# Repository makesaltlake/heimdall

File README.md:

# Heimdall

Heimdall is [Make Salt Lake](https://makesaltlake.org)'s member management and access control system. It consists of a few different parts:

  - [Firmware](firmware) intended to run on an [ESP32](https://en.wikipedia.org/wiki/ESP32), one per door or other device that needs access control.
  - [PCB designs](hardware) that can be used to make the physical badge readers.

### 
Join [Make Salt Lake's Slack team](https://slack.makesaltlake.org/), then head over to [#rfid-strikeforce](https://app.slack.com/client/T16JZCGBY/CGDLBCCCT) if you'd like to get in touch.

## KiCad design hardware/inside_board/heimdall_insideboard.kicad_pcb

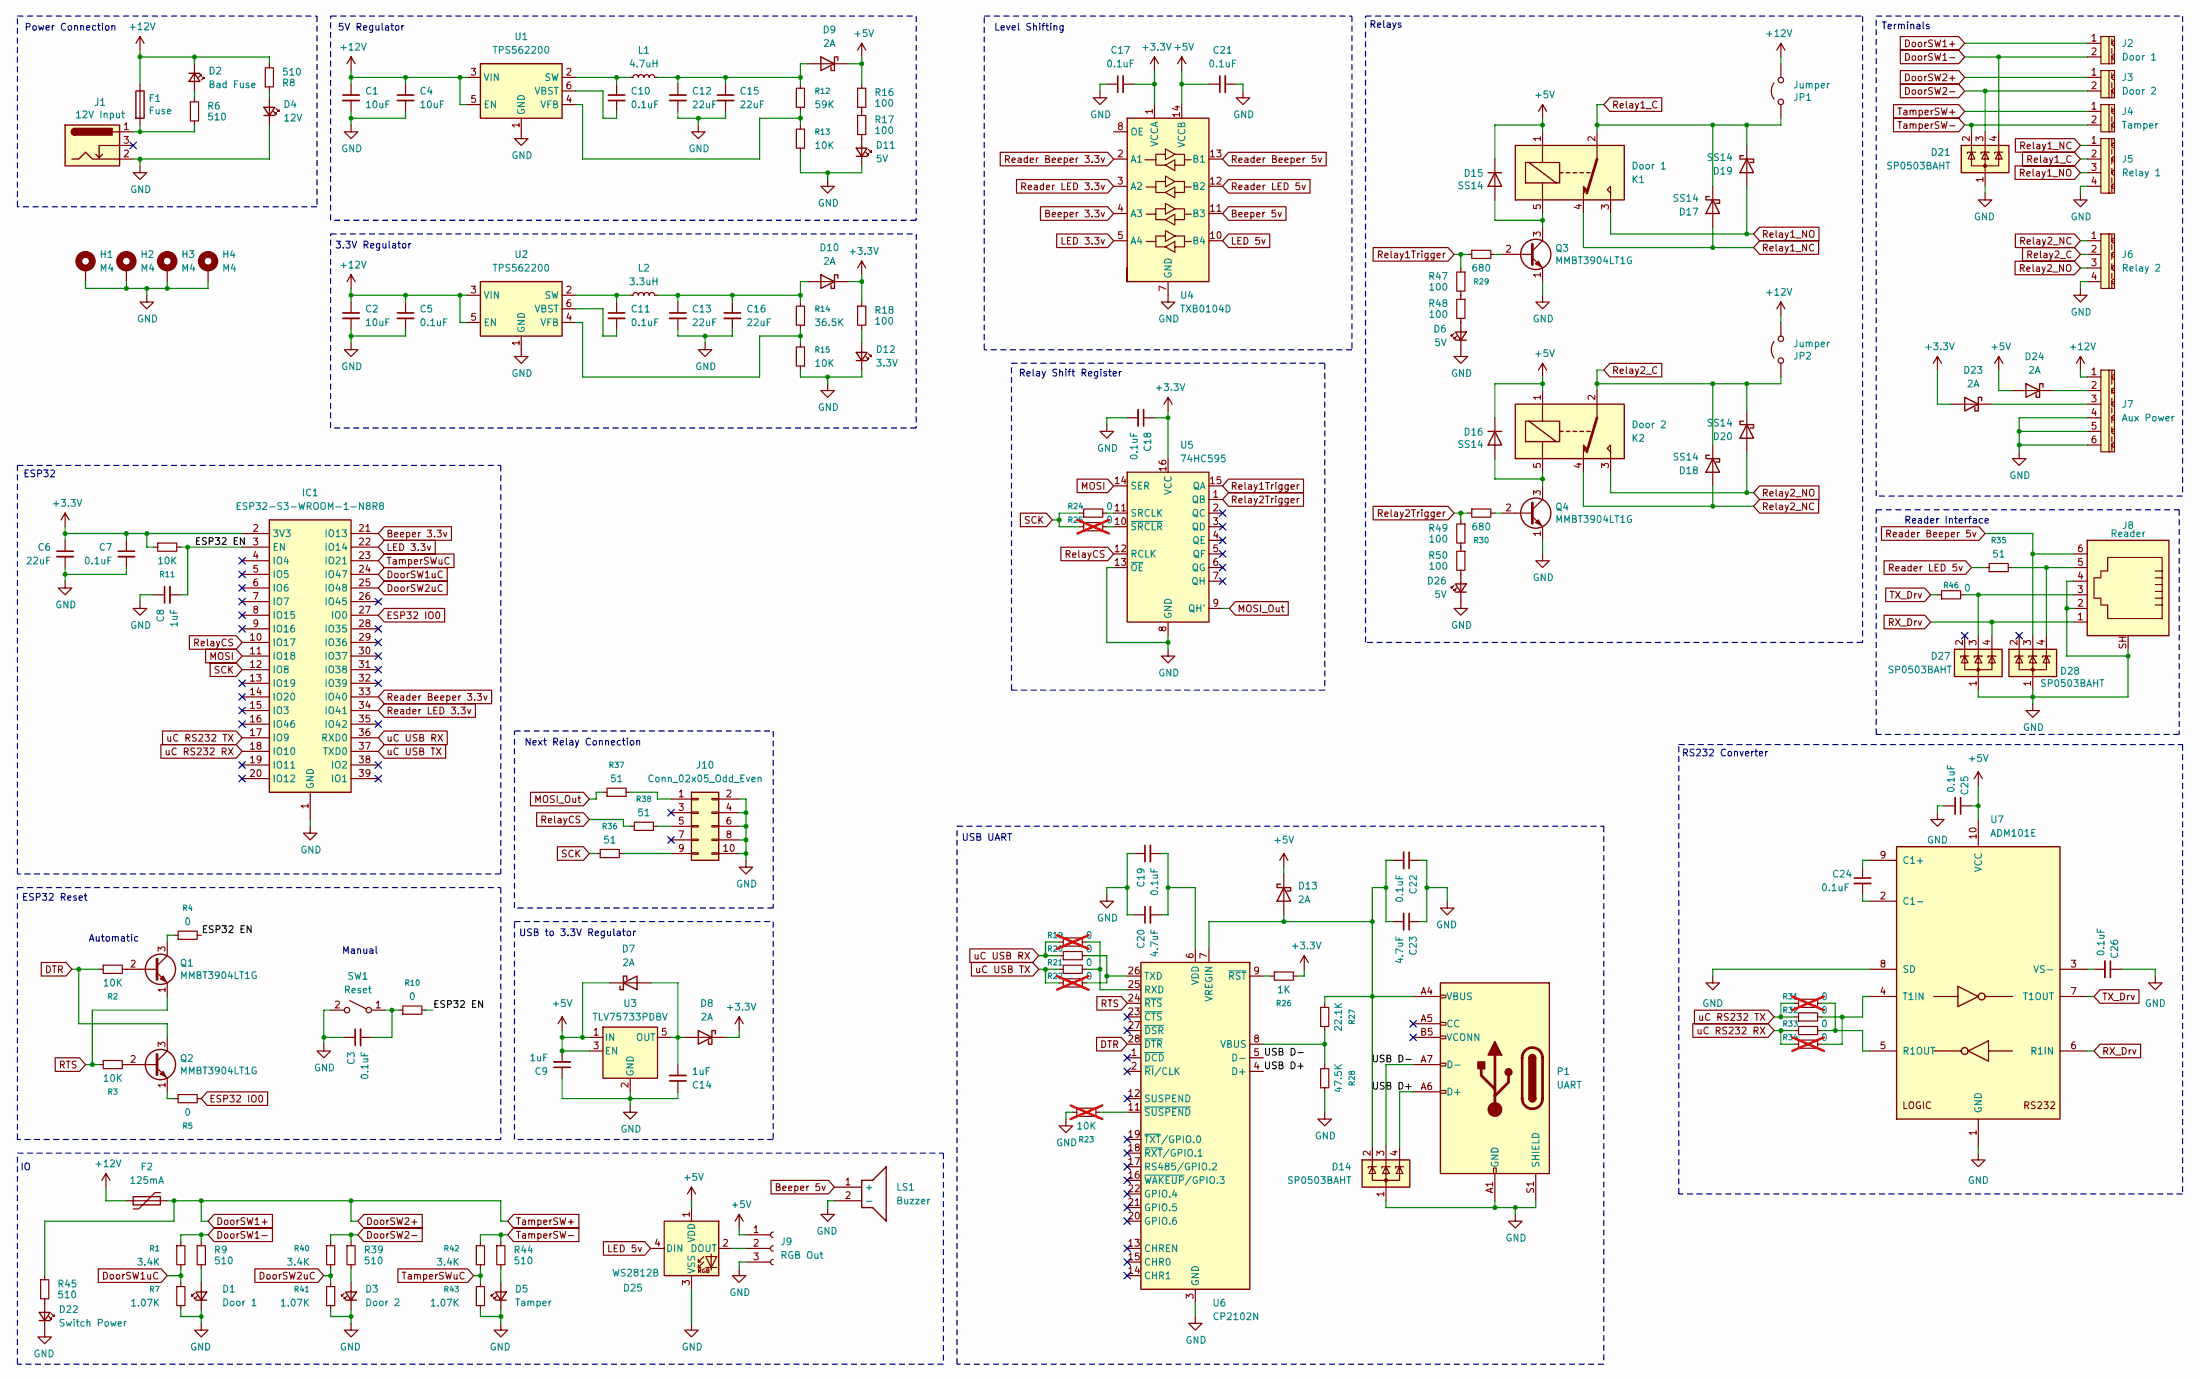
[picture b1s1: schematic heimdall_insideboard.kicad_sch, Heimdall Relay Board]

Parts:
C1, C2, C4: 10uF; C_0805_2012Metric
C3, C5, C7, C10, C11, C17, C18, C19, C21, C22, C24, C25, C26: 0.1uF; C_0805_2012Metric
C6, C12, C13, C15, C16: 22uF; C_0805_2012Metric
C8, C9, C14: 1uF; C_0805_2012Metric
C20, C23: 4.7uF; C_0805_2012Metric
D1: Door 1; LED_0805_2012Metric
D2: Bad Fuse; LED_0805_2012Metric
D3: Door 2; LED_0805_2012Metric
D4: 12V; LED_0805_2012Metric
D5: Tamper; LED_0805_2012Metric
D6, D11, D26: 5V; LED_0805_2012Metric
D7, D8, D9, D10, D13, D23, D24: 2A; D_SMB
D12: 3.3V; LED_0805_2012Metric
D14, D21, D27, D28: SP0503BAHT; SOT-143
D15, D16, D17, D18, D19, D20: SS14; D_SMA
D22: Switch Power; LED_0805_2012Metric
D25: WS2812B; LED_WS2812B_PLCC4_5.0x5.0mm_P3.2mm
F1: Fuse; Fuseholder_Clip-5x20mm_Littelfuse_521_Lateral_P17.00x5.00mm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
F2: 125mA; Fuse_1206_3216Metric
H1, H2, H3, H4: M4; MountingHole_4.3mm_M4_Pad_Via
IC1: ESP32-S3-WROOM-1-N8R8; ESP32S3WROOM1N8R8; Mouser Part Number 356-EP32S3WROOM1N8R8
J1: 12V Input; BarrelJack_Wuerth_6941xx301002
J2: Door 1; 1759017
J3: Door 2; 1759017
J4: Tamper; 1759017
J5: Relay 1; 1759033
J6: Relay 2; 1759033
J7: Aux Power; 1759059
J8: Reader; CRJ0241TH
J9: RGB Out; PinHeader_1x03_P2.54mm_Vertical
J10: Conn_02x05_Odd_Even; 75869-101LF
JP1, JP2: Jumper; PinHeader_1x03_P2.54mm_Vertical
K1: Door 1; G6RN17EASICFHADC5; Manufacturer_Part_Number G6RN-17-E-ASI-CF-HA DC5
K2: Door 2; G6RN17EASICFHADC5; Manufacturer_Part_Number G6RN-17-E-ASI-CF-HA DC5
L1: 4.7uH; SRR1260A4R7Y
L2: 3.3uH; SRR1260A4R7Y
LS1: Buzzer; CMT1075SMTTR; Mouser Part Number 490-CMT-1075-SMT-TR
P1: UART; USB4920-00-A
Q1, Q2, Q3, Q4: MMBT3904LT1G; SOT-23-3
R1, R40, R42: 3.4K; R_0805_2012Metric
R2, R3, R11, R13, R15: 10K; R_0805_2012Metric
R4, R5, R10, R20, R21, R24, R32, R33, R46: 0; R_0805_2012Metric
R6, R8, R9, R39, R44, R45: 510; R_0805_2012Metric
R7, R41, R43: 1.07K; R_0805_2012Metric
R12: 59K; R_0805_2012Metric
R14: 36.5K; R_0805_2012Metric
R16, R17, R18, R47, R48, R49, R50: 100; R_0805_2012Metric
R19, R22, R25, R31, R34: 0; R_0805_2012Metric; not fitted
R23: 10K; R_0805_2012Metric; not fitted
R26: 1K; R_0805_2012Metric
R27: 22.1K; R_0805_2012Metric
R28: 47.5K; R_0805_2012Metric
R29, R30: 680; R_0805_2012Metric
R35, R36, R37, R38: 51; R_0805_2012Metric
SW1: Reset; SW_SPST_Omron_B3FS-100xP
U1, U2: TPS562200; SOT-23-6
U3: TLV75733PDBV; SOT-23-5
U4: TXB0104D; SOIC-14_3.9x8.7mm_P1.27mm
U5: 74HC595; SOIC-16W_7.5x10.3mm_P1.27mm
U6: CP2102N; QFN-28-1EP_5x5mm_P0.5mm_EP3.35x3.35mm
U7: ADM101E; MSOP-10_3x3mm_P0.5mm

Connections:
+3.3V: C6.1, C7.1, C17.2, C18.1, D8.1 (K), D10.1 (K), D23.2 (A), IC1.2 (3V3), R11.1, R18.1, R26.2, U4.1 (VCCA), U5.16 (VCC)
+5V: C9.2, C21.1, C25.1, D7.1 (K), D9.1 (K), D13.1 (K), D15.1 (K), D16.1 (K), D24.2 (A), D25.1 (VDD), J9.1, K1.1, K2.1, R16.1, U3.1 (IN), U3.3 (EN), U4.14 (VCCB), U7.10 (VCC)
+12V: C1.1, C2.1, C4.1, C5.1, D2.1 (K), F1.1, F2.1, J7.1, JP1.1 (A), JP2.1 (A), R8.2, U1.3 (VIN), U1.5 (EN), U2.3 (VIN), U2.5 (EN)
/ESP32 EN: C8.2, IC1.3 (EN), R4.2, R10.2, R11.2
/USB D+: D14.4 (K), P1.A6 (D+), U6.4 (D+)
/USB D-: D14.3 (K), P1.A7 (D-), U6.5 (D-)
Beeper 3.3v: IC1.21 (IO13), U4.4 (A3)
Beeper 5v: LS1.1 (+), U4.11 (B3)
DTR: Q2.3 (C), R2.1, U6.28 (~DTR)
DoorSW1+: F2.2, J2.1, J3.1, J4.1, R45.1
DoorSW1-: D21.4 (K), J2.2, R1.1, R9.1
DoorSW1uC: IC1.24 (IO47), R1.2, R7.1
DoorSW2-: D21.3 (K), J3.2, R39.1, R40.1
DoorSW2uC: IC1.25 (IO48), R40.2, R41.1
ESP32 IO0: IC1.27 (IO0), R5.2
GND: C1.2, C2.2, C3.1, C4.2, C5.2, C6.2, C7.2, C8.1, C9.1, C12.2, C13.2, C14.1, C15.2, C16.2, C17.1, C18.2, C19.1, C20.1, C21.2, C22.1, C23.1, C25.2, C26.1, D1.1 (K), D3.1 (K), D4.1 (K), D5.1 (K), D6.1 (K), D11.1 (K), D12.1 (K), D14.1 (A), D21.1 (A), D22.1 (K), D25.3 (VSS), D26.1 (K), D27.1 (A), D28.1 (A), H1.1, H2.1, H3.1, H4.1, IC1.1 (GND), J1.2, J5.4, J6.4, J7.4, J7.5, J7.6, J8.2, J8.4, J8.SH, J9.3, J10.2, J10.4, J10.6, J10.8, J10.10, LS1.2 (-), P1.A1 (GND), P1.A12 (GND), P1.B1 (GND), P1.B12 (GND), P1.S1 (SHIELD), Q3.1 (E), Q4.1 (E), R7.2, R13.1, R15.1, R23.1, R28.1, R41.2, R43.2, SW1.2 (B), U1.1 (GND), U2.1 (GND), U3.2 (GND), U4.7 (GND), U5.8 (GND), U5.13 (~OE), U6.3 (GND), U6.29 (GND), U7.1 (GND), U7.8 (SD)
LED 3.3v: IC1.22 (IO14), U4.5 (A4)
LED 5v: D25.4 (DIN), U4.10 (B4)
MOSI: IC1.11 (IO18), U5.14 (SER)
MOSI_Out: R37.1, U5.9 (QH')
unnamed: D1.2 (A), R9.2
unnamed: D2.2 (A), R6.1
unnamed: D3.2 (A), R39.2
unnamed: D4.2 (A), R8.1
unnamed: D5.2 (A), R44.2
unnamed: D6.2 (A), R48.2
unnamed: C14.2, D7.2 (A), D8.2 (A), U3.5 (OUT)
unnamed: C12.1, C15.1, D9.2 (A), L1.2, R12.2
unnamed: C13.1, C16.1, D10.2 (A), L2.2, R14.2
unnamed: D11.2 (A), R17.2
unnamed: D12.2 (A), R18.2
unnamed: C22.2, C23.2, D13.2 (A), D14.2 (K), P1.A4 (VBUS), P1.A9 (VBUS), P1.B4 (VBUS), P1.B9 (VBUS), R27.2, U6.7 (VREGIN)
unnamed: D15.2 (A), K1.5, Q3.3 (C)
unnamed: D16.2 (A), K2.5, Q4.3 (C)
unnamed: D22.2 (A), R45.2
unnamed: D23.1 (K), J7.3
unnamed: D24.1 (K), J7.2
unnamed: D25.2 (DOUT), J9.2
unnamed: D26.2 (A), R50.2
unnamed: D27.3 (K), J8.3, R46.2
unnamed: D28.4 (K), J8.5, R35.2
unnamed: F1.2, J1.1, R6.2
unnamed: J10.1, R37.2
unnamed: J10.5, R38.2
unnamed: J10.9, R36.2
unnamed: Q1.2 (B), R2.2
unnamed: Q1.3 (C), R4.1
unnamed: Q2.2 (B), R3.2
unnamed: Q2.1 (E), R5.1
unnamed: Q3.2 (B), R29.2
unnamed: Q4.2 (B), R30.2
unnamed: R16.2, R17.1
unnamed: R47.2, R48.1
unnamed: R49.2, R50.1
unnamed: C3.2, R10.1, SW1.1 (A)
unnamed: C10.1, L1.1, U1.2 (SW)
unnamed: C10.2, U1.6 (VBST)
unnamed: R12.1, R13.2, U1.4 (VFB)
unnamed: C11.1, L2.1, U2.2 (SW)
unnamed: C11.2, U2.6 (VBST)
unnamed: R14.1, R15.2, U2.4 (VFB)
unnamed: R24.2, U5.11 (SRCLK)
unnamed: R25.2, U5.10 (~SRCLR)
unnamed: R19.2, R21.2, U6.25 (RXD)
unnamed: R20.2, R22.2, U6.26 (TXD)
unnamed: R27.1, R28.2, U6.8 (VBUS)
unnamed: C19.2, C20.2, U6.6 (VDD)
unnamed: R26.1, U6.9 (~RST)
unnamed: R23.2, U6.11 (~SUSPEND)
unnamed: C24.1, U7.9 (C1+)
unnamed: C24.2, U7.2 (C1-)
unnamed: R31.2, R33.2, U7.5 (R1OUT)
unnamed: R32.2, R34.2, U7.4 (T1IN)
unnamed: C26.2, U7.3 (VS-)
RTS: Q1.1 (E), R3.1, U6.24 (~RTS)
RX_Drv: D27.4 (K), J8.1, U7.6 (R1IN)
Reader Beeper 3.3v: IC1.33 (IO40), U4.2 (A1)
Reader Beeper 5v: D28.3 (K), J8.6, U4.13 (B1)
Reader LED 3.3v: IC1.34 (IO41), U4.3 (A2)
Reader LED 5v: R35.1, U4.12 (B2)
Relay1Trigger: R29.1, R47.1, U5.15 (QA)
Relay1_C: D17.1 (K), D19.1 (K), J5.2, JP1.2 (B), K1.2
Relay1_NC: D17.2 (A), J5.1, K1.4
Relay1_NO: D19.2 (A), J5.3, K1.3
Relay2Trigger: R30.1, R49.1, U5.1 (QB)
Relay2_C: D18.1 (K), D20.1 (K), J6.2, JP2.2 (B), K2.2
Relay2_NC: D18.2 (A), J6.1, K2.4
Relay2_NO: D20.2 (A), J6.3, K2.3
RelayCS: IC1.10 (IO17), R38.1, U5.12 (RCLK)
SCK: IC1.12 (IO8), R24.1, R25.1, R36.1
TX_Drv: R46.1, U7.7 (T1OUT)
TamperSW-: D21.2 (K), J4.2, R42.1, R44.1
TamperSWuC: IC1.23 (IO21), R42.2, R43.1
uC RS232 RX: IC1.18 (IO10), R33.1, R34.1
uC RS232 TX: IC1.17 (IO9), R31.1, R32.1
uC USB RX: IC1.36 (RXD0), R19.1, R20.1
uC USB TX: IC1.37 (TXD0), R21.1, R22.1

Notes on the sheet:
Power Connection
Relay Shift Register
Automatic
RS232 Converter
ESP32 Reset
USB to 3.3V Regulator
Terminals
Next Relay Connection
Manual
3.3V Regulator
5V Regulator
Reader Interface
Relays
Level Shifting
USB UART
ESP32

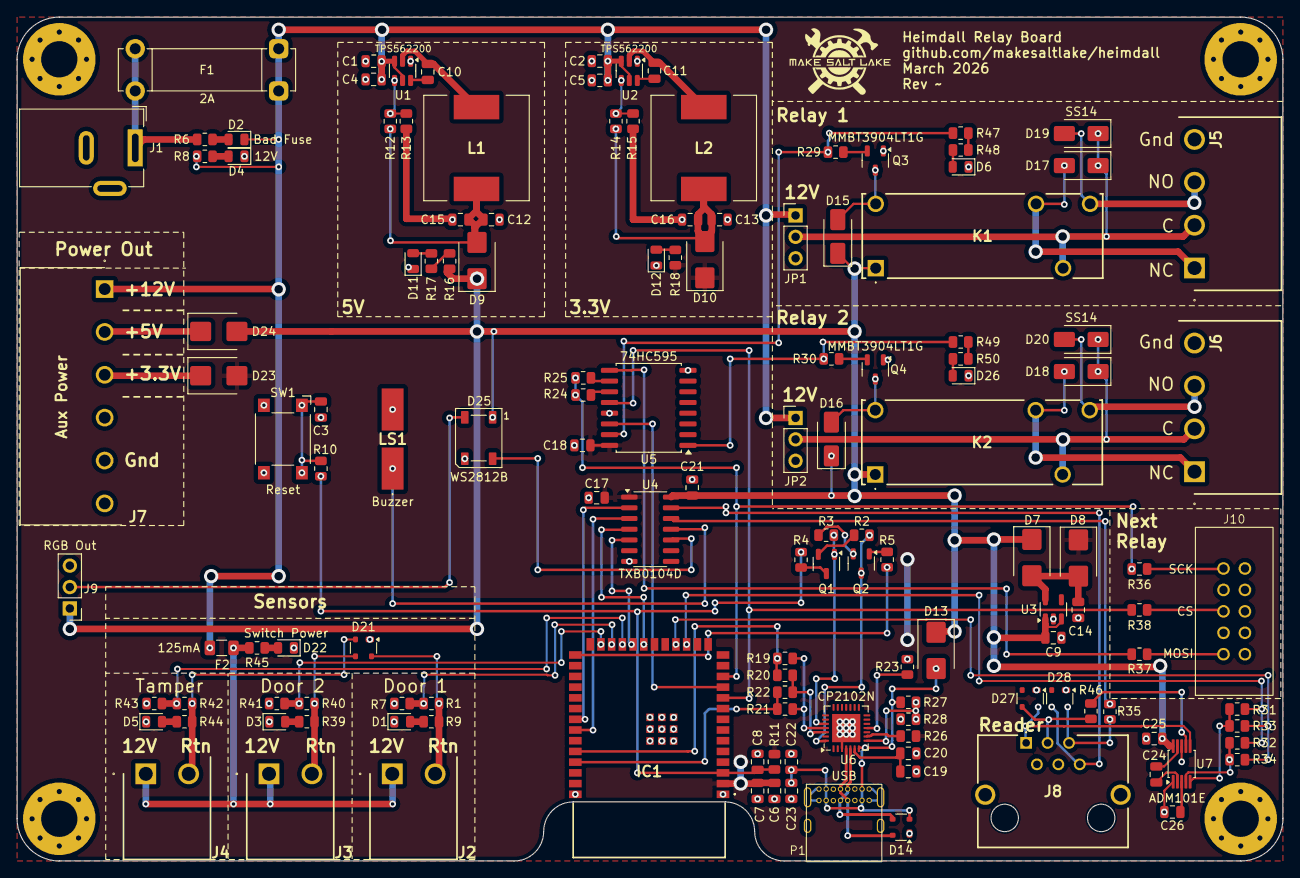
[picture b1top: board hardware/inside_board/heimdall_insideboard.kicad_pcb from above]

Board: 2 copper layers, 150.0 x 100.0 mm, 141 parts (0 on the bottom side), 97 nets.

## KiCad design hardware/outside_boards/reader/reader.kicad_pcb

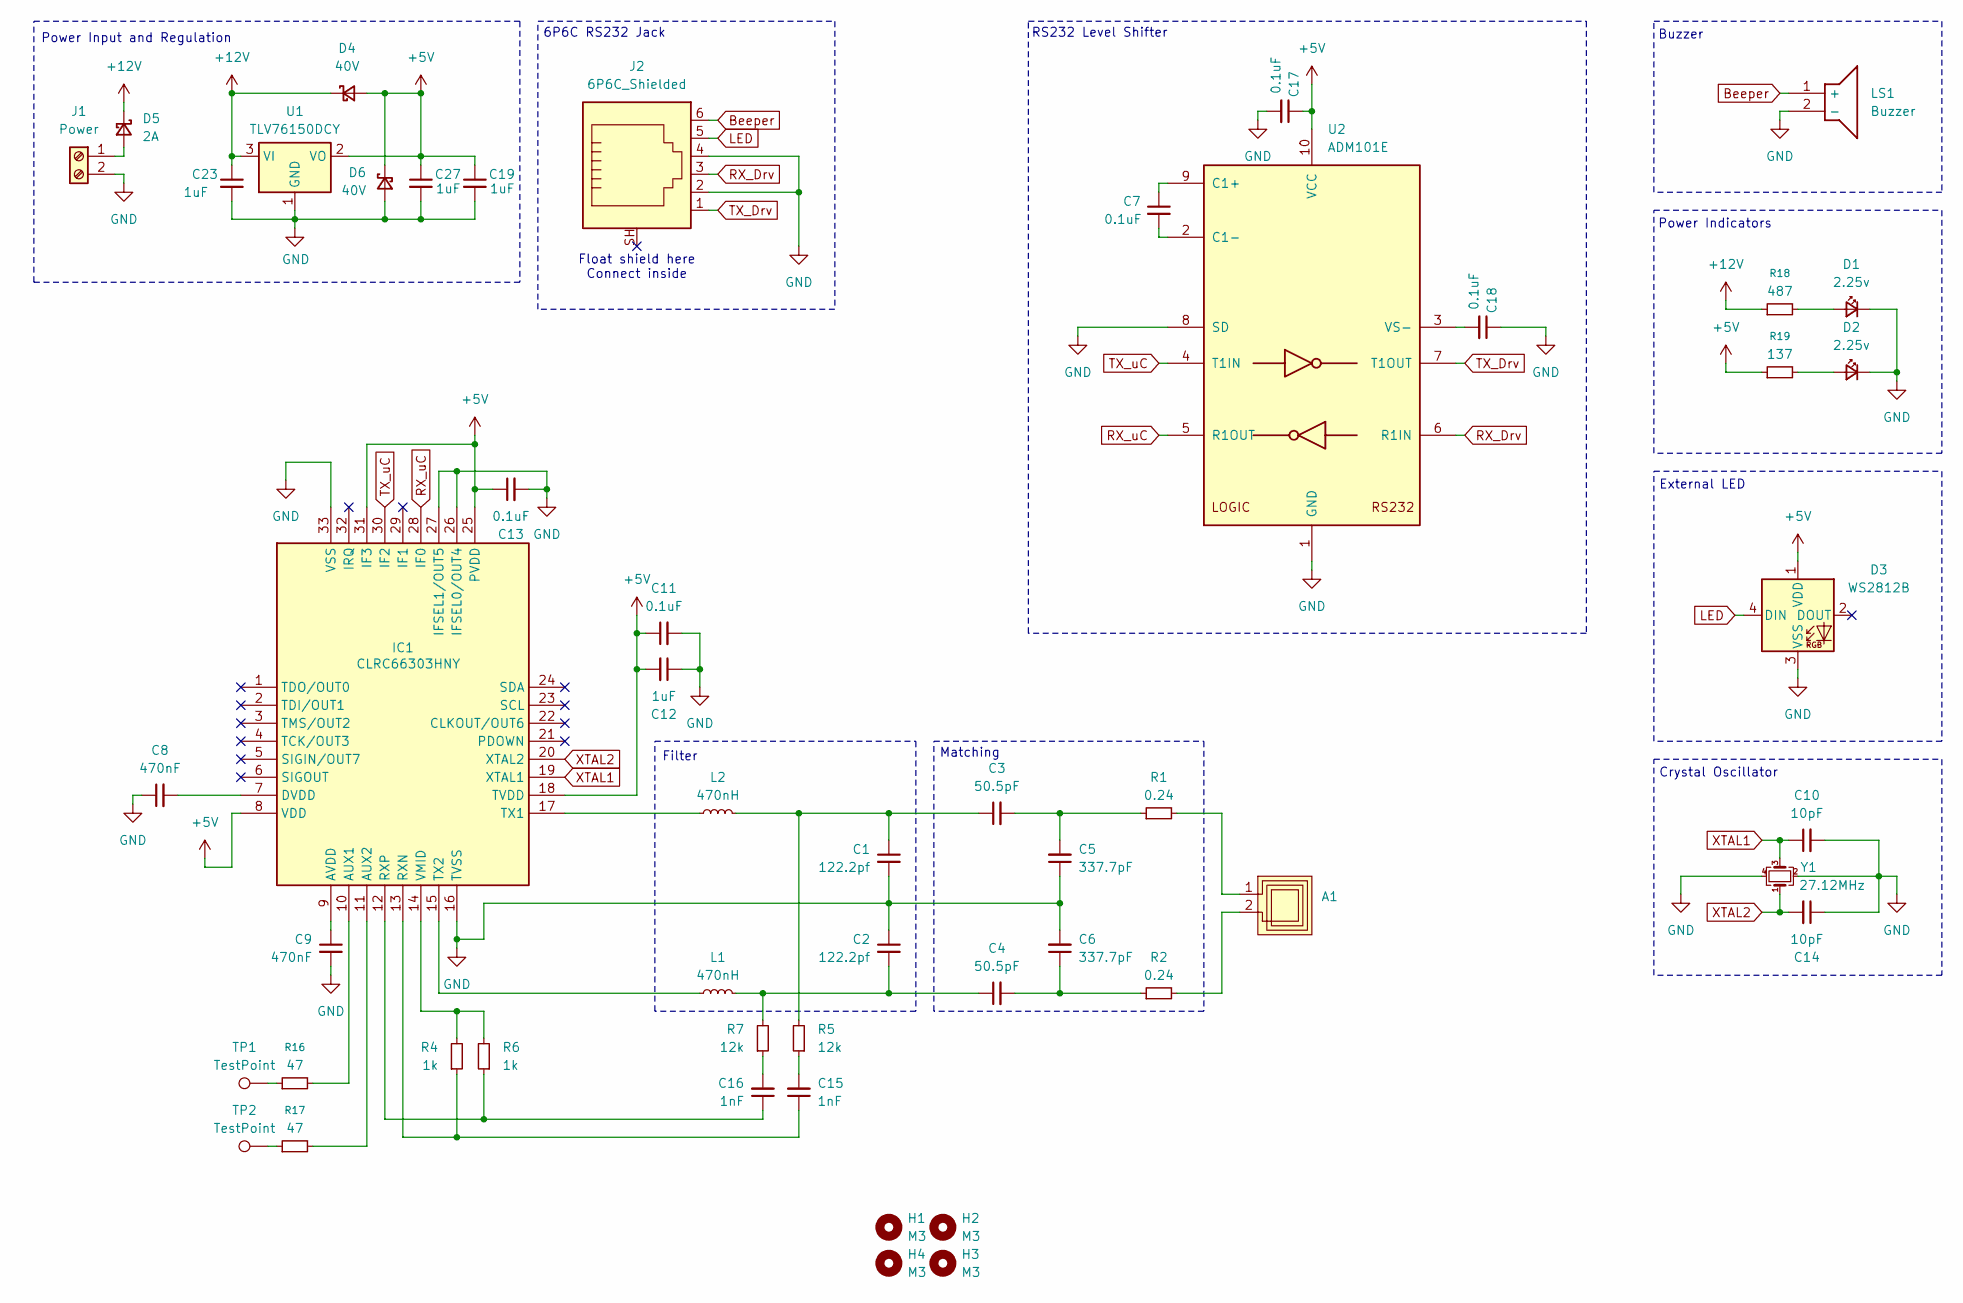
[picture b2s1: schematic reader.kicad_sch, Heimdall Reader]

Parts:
A1: Anetnna_50x50
C1, C2: 122.2pf; C_0805_2012Metric
C3, C4: 50.5pF; C_0805_2012Metric
C5, C6: 337.7pF; C_0805_2012Metric
C7, C11, C13, C17, C18: 0.1uF; C_0805_2012Metric
C8, C9: 470nF; C_0805_2012Metric
C10, C14: 10pF; C_0805_2012Metric
C12, C19, C23, C27: 1uF; C_0805_2012Metric
C15, C16: 1nF; C_0805_2012Metric
D1, D2: 2.25v; LED_0805_2012Metric
D3: WS2812B; LED_WS2812B_PLCC4_5.0x5.0mm_P3.2mm
D4, D6: 40V; D_1206_3216Metric
D5: 2A; D_1206_3216Metric
H1, H2, H3, H4: M3; MountingHole_3.2mm_M3
IC1: CLRC66303HNY; QFN50P500X500X100-33N; Mouser Part Number 771-CLRC66303HNY
J1: Power; 1991095
J2: 6P6C_Shielded; CRJ0241TH
L1, L2: 470nH; L_0805_2012Metric
LS1: Buzzer; CMT1075SMTTR; Mouser Part Number 490-CMT-1075-SMT-TR
R1, R2: 0.24; R_0805_2012Metric
R4, R6: 1k; R_0805_2012Metric
R5, R7: 12k; R_0805_2012Metric
R16, R17: 47; R_0805_2012Metric
R18: 487; R_0805_2012Metric
R19: 137; R_0805_2012Metric
TP1, TP2: TestPoint; TestPoint_Pad_D1.5mm
U1: TLV76150DCY; SOT-223-3_TabPin2
U2: ADM101E; MSOP-10_3x3mm_P0.5mm
Y1: 27.12MHz; Crystal_SMD_3225-4Pin_3.2x2.5mm

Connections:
+5V: C11.1, C12.2, C13.1, C17.1, C19.1, C27.1, D3.1 (VDD), D4.2 (A), D6.1 (K), IC1.8 (VDD), IC1.18 (TVDD), IC1.25 (PVDD), IC1.31 (IF3), R19.1, U1.2 (VO), U2.10 (VCC)
+12V: C23.1, D4.1 (K), D5.1 (K), R18.1, U1.3 (VI)
Beeper: J2.6, LS1.1 (+)
GND: C1.2, C2.1, C5.1, C6.2, C8.1, C9.2, C10.2, C11.2, C12.1, C13.2, C14.1, C17.2, C18.1, C19.2, C23.2, C27.2, D1.1 (K), D2.1 (K), D3.3 (VSS), D6.2 (A), IC1.16 (TVSS), IC1.26 (IFSEL0/OUT4), IC1.27 (IFSEL1/OUT5), IC1.33 (VSS), J1.2, J2.2, J2.4, LS1.2 (-), U1.1 (GND), U2.1 (GND), U2.8 (SD), Y1.2, Y1.4
LED: D3.4 (DIN), J2.5
unnamed: A1.1, R1.2
unnamed: A1.2, R2.2
unnamed: C1.1, C3.1, L2.2, R5.2
unnamed: C2.2, C4.1, L1.2, R7.2
unnamed: C3.2, C5.2, R1.1
unnamed: C4.2, C6.1, R2.1
unnamed: C15.2, R5.1
unnamed: C16.2, R7.1
unnamed: D1.2 (A), R18.2
unnamed: D2.2 (A), R19.2
unnamed: D5.2 (A), J1.1
unnamed: IC1.10 (AUX1), R16.2
unnamed: IC1.11 (AUX2), R17.2
unnamed: C9.1, IC1.9 (AVDD)
unnamed: C8.2, IC1.7 (DVDD)
unnamed: C15.1, IC1.13 (RXN), R4.1
unnamed: C16.1, IC1.12 (RXP), R6.1
unnamed: IC1.17 (TX1), L2.1
unnamed: IC1.15 (TX2), L1.1
unnamed: IC1.14 (VMID), R4.2, R6.2
unnamed: R16.1, TP1.1
unnamed: R17.1, TP2.1
unnamed: C7.1, U2.9 (C1+)
unnamed: C7.2, U2.2 (C1-)
unnamed: C18.2, U2.3 (VS-)
RX_Drv: J2.3, U2.6 (R1IN)
RX_uC: IC1.28 (IF0), U2.5 (R1OUT)
TX_Drv: J2.1, U2.7 (T1OUT)
TX_uC: IC1.30 (IF2), U2.4 (T1IN)
XTAL1: C10.1, IC1.19 (XTAL1), Y1.3
XTAL2: C14.2, IC1.20 (XTAL2), Y1.1

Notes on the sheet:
External LED
Crystal Oscillator
Power Indicators
Matching
Float shield here Connect inside
Buzzer
6P6C RS232 Jack
Power Input and Regulation
RS232 Level Shifter
Filter

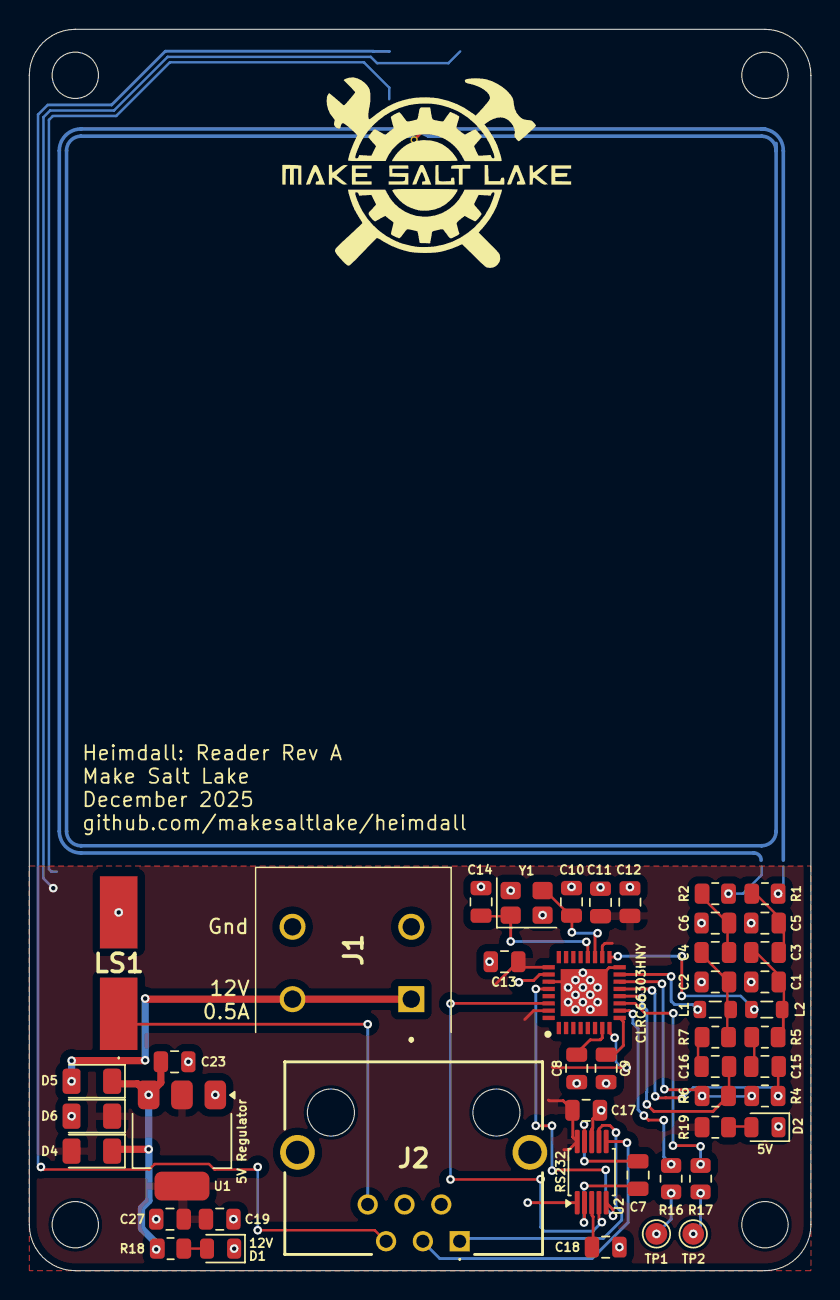
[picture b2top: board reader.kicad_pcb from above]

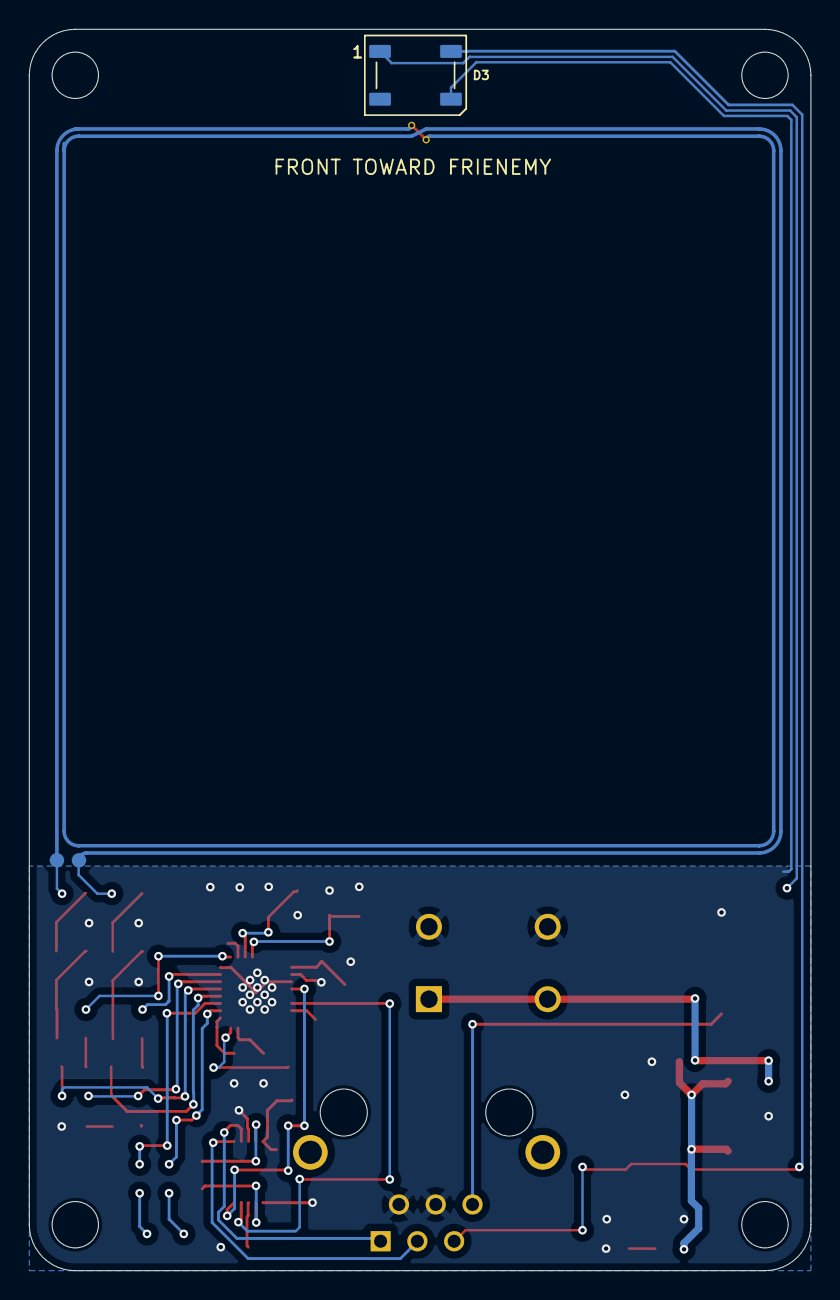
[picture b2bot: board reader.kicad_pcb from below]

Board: 2 copper layers, 54.0 x 85.7 mm, 53 parts (2 on the bottom side), 36 nets.

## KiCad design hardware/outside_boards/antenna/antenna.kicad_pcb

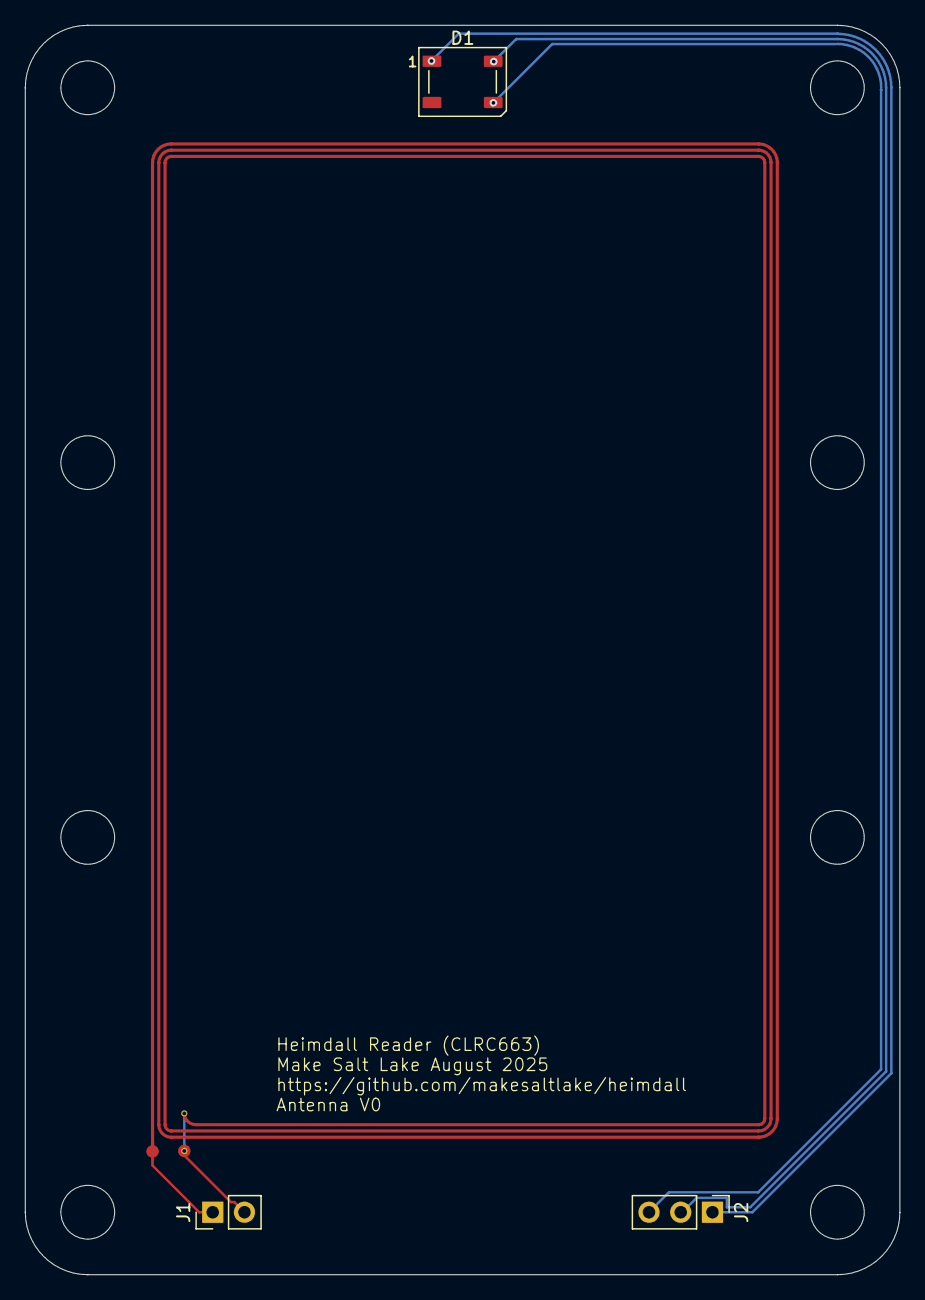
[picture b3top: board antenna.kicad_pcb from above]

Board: 2 copper layers, 70.0 x 100.0 mm, 4 parts (0 on the bottom side), 5 nets.

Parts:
A1: Anetnna_50x80
D1: WS2812B; LED_WS2812B_PLCC4_5.0x5.0mm_P3.2mm
J1: Jumper; PinHeader_1x02_P2.54mm_Vertical
J2: Conn_01x03_Pin; PinHeader_1x03_P2.54mm_Vertical

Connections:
unnamed: D1.4 (DIN), J2.2
unnamed: D1.1 (VDD), J2.1
unnamed: D1.3 (VSS), J2.3
unnamed: A1.1, J1.1
unnamed: A1.2, J1.2

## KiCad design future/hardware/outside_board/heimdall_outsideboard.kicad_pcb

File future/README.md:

This directory contains work-in-progress stuff for Heimdall's future.

Mainly, it contains firmware for the badge reader boards that supports Mifare Classic RFID cards. Those are less easily
cloned than the EM4100 cards we're using right now, so at some point we'd like to switch to using them.

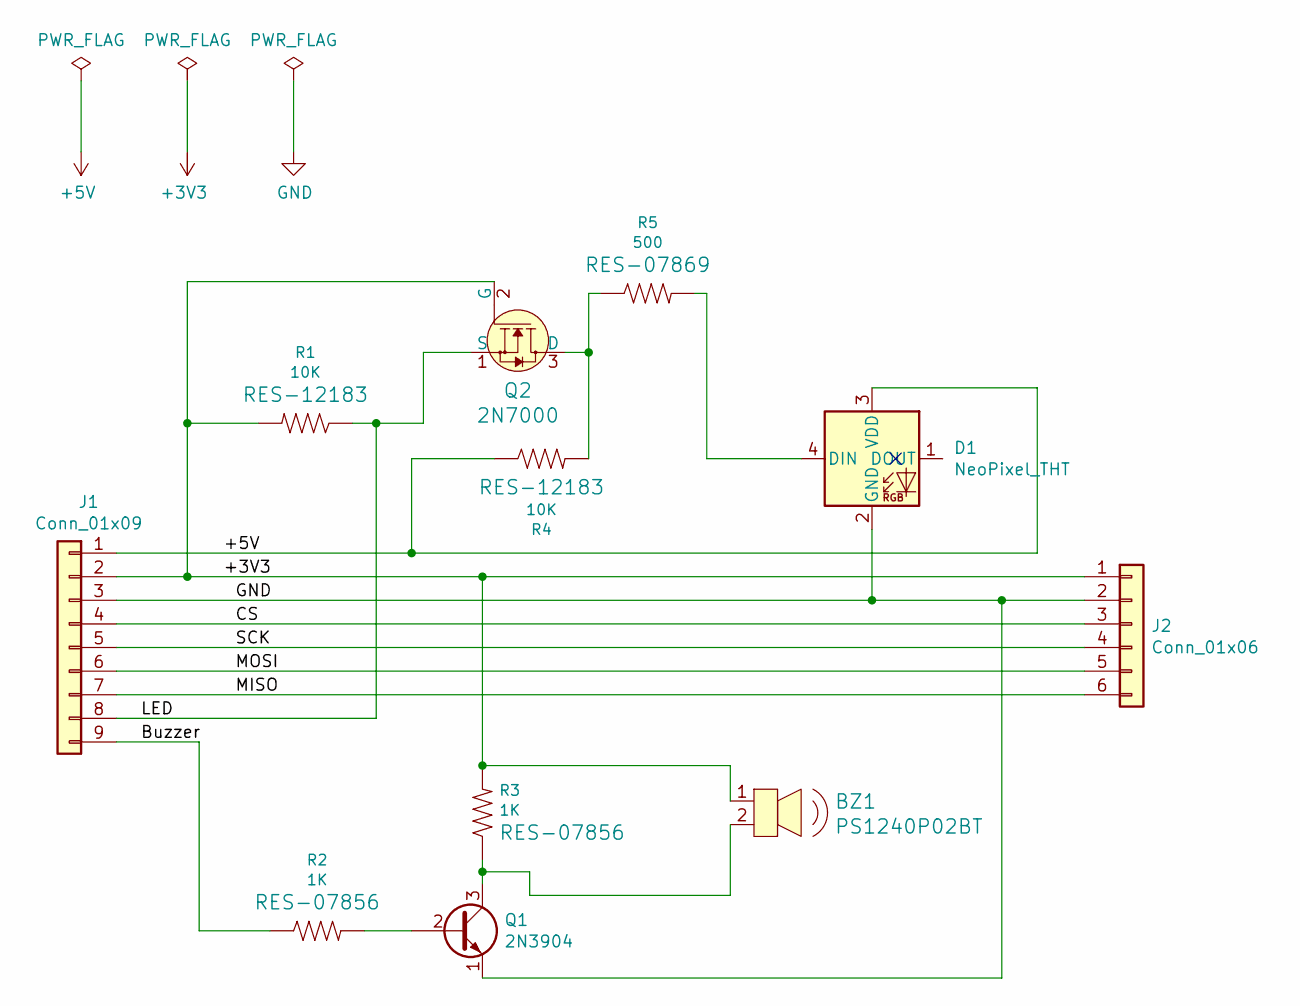
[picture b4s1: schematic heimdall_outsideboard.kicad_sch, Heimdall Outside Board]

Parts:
BZ1: PS1240P02BT; Piezo_Transducer_THT_PS1240P02BT; MPN PS1240P02BT; Digi-Key_PN 445-2525-1-ND
D1: NeoPixel_THT; LED_D5.0mm-4_RGB
J1: Conn_01x09; PinHeader_1x09_P2.54mm_Vertical
J2: Conn_01x06; PinHeader_1x06_P2.54mm_Vertical
Q1: 2N3904; TO-92_Inline
Q2: 2N7000; TO-92_Inline; MPN 2N7000; Digi-Key_PN 2N7000FS-ND
R1, R4: 10K; R_Axial_DIN0207_L6.3mm_D2.5mm_P10.16mm_Horizontal
R2, R3: 1K; R_Axial_DIN0207_L6.3mm_D2.5mm_P10.16mm_Horizontal
R5: 500; R_Axial_DIN0207_L6.3mm_D2.5mm_P10.16mm_Horizontal

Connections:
+3V3: BZ1.1, J1.2, J2.1, Q2.2 (G), R1.2, R3.2
+5V: D1.3 (VDD), J1.1, R4.1
/Buzzer: J1.9, R2.1
/CS: J1.4, J2.3
/LED: J1.8, Q2.1 (S), R1.1
/MISO: J1.7, J2.6
/MOSI: J1.6, J2.5
/SCK: J1.5, J2.4
GND: D1.2 (GND), J1.3, J2.2, Q1.1 (E)
unnamed: BZ1.2, Q1.3 (C), R3.1
unnamed: Q1.2 (B), R2.2
unnamed: Q2.3 (D), R4.2, R5.1
unnamed: D1.4 (DIN), R5.2

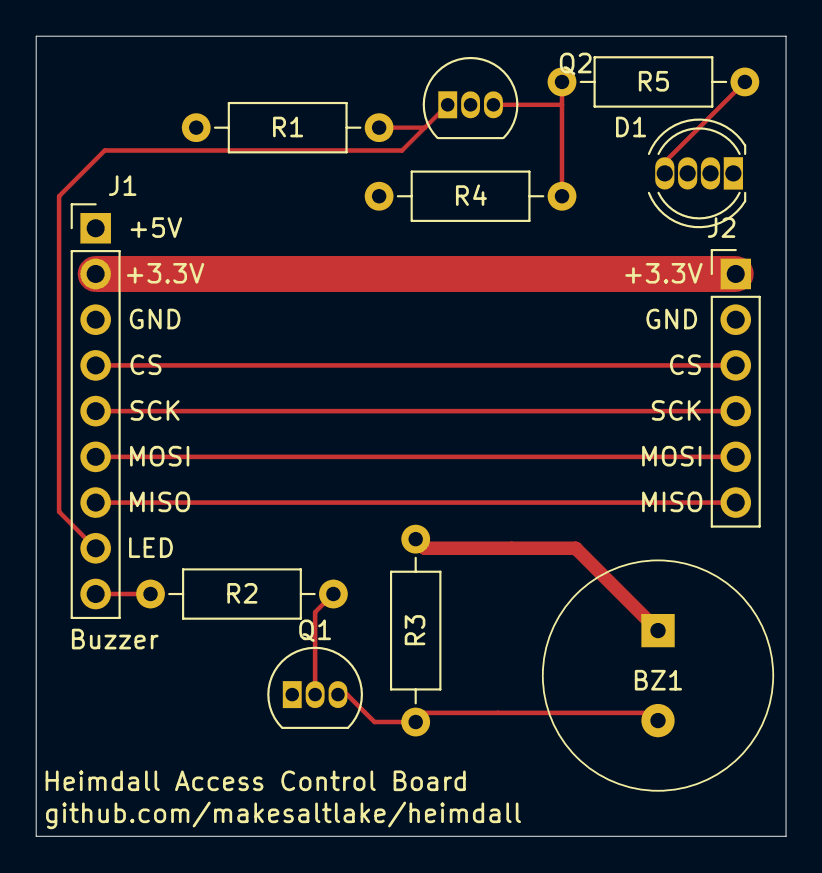
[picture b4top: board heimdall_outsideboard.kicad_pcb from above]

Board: 4 copper layers, 41.7 x 44.5 mm, 11 parts (0 on the bottom side), 13 nets.

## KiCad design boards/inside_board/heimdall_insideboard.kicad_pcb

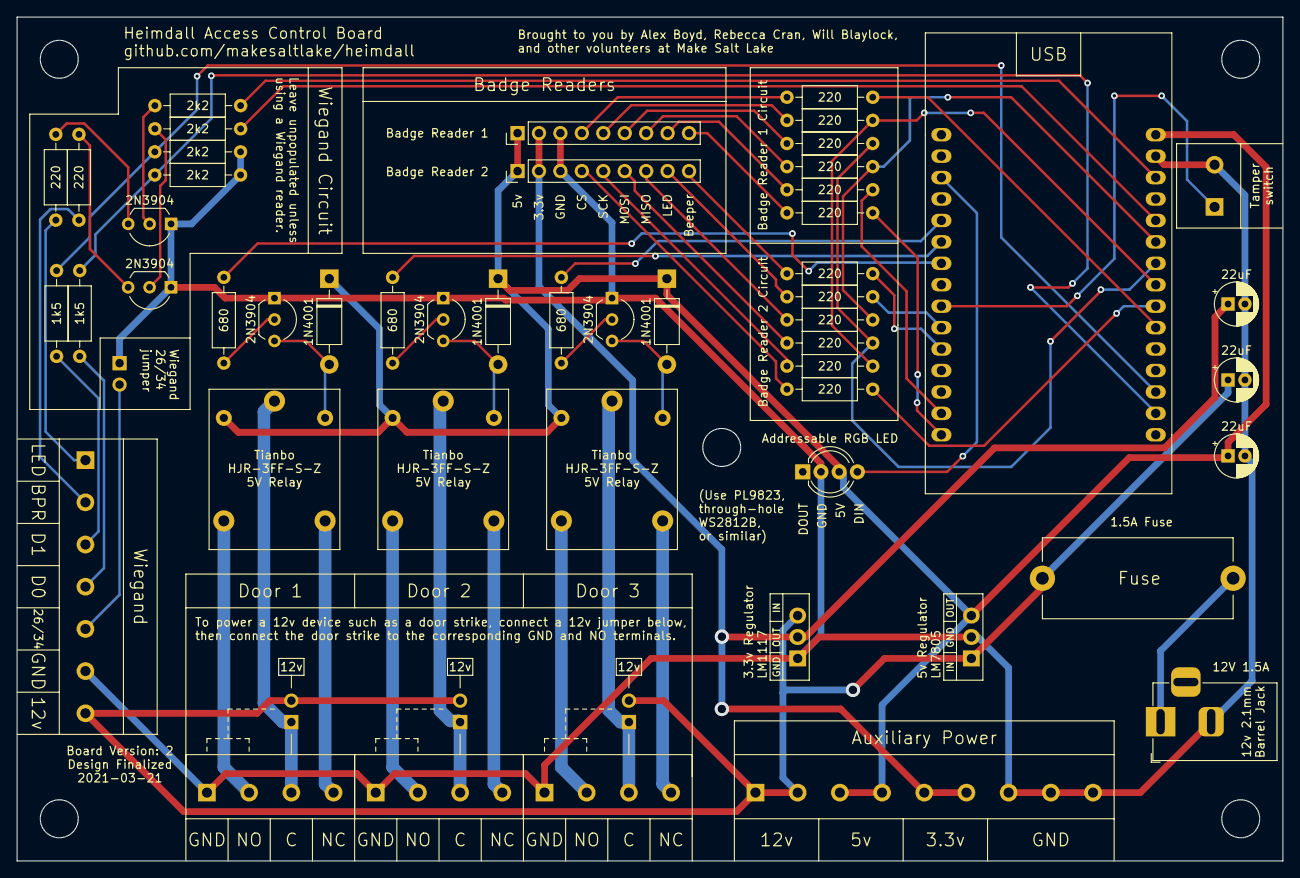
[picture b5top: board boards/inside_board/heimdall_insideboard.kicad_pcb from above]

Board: 2 copper layers, 150.0 x 100.0 mm, 55 parts (0 on the bottom side), 59 nets.

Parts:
2N3904, 2N3904#2, 2N3904#3, 2N3904#4, 2N3904#5: 2N3904; JW_TO-92_Inline_Wide_Silkscreen_Part_Number_Only
Addressable RGB LED: NeoPixel_THT; LED_D5.0mm-4_RGB_Wide_Pins
C1, C2, C3: 22uF; CP_Radial_D5.0mm_P2.00mm
D1, D2, D3: 1N4001; JW_D_DO-41_SOD81_P10.16mm_Horizontal_Silkscreen_Part_Number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
F1: Fuse; Fuseholder_Cylinder-5x20mm_Stelvio-Kontek_PTF78_Horizontal_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
J1: Barrel_Jack_Switch; BarrelJack_Horizontal
J2, J4, J6: Screw_Terminal_01x04; PinHeader_JW_1x04_P5.00mm_Vertical
J3, J5: Conn_01x09; PinHeader_1x09_P2.54mm_Vertical
J7: Screw_Terminal_01x06; PinHeader_JW_1x07_P5.00mm_Vertical
J8: Screw_Terminal_01x09; PinHeader_JW_1x09_P5.00mm_Vertical
J9: Screw_Terminal_01x02; PinHeader_JW_1x02_P5.00mm_Vertical
JP1, JP2, JP3, JP4: Jumper; PinHeader_JW_1x02_P2.54mm_Vertical_Without_Silkscreen
K1, K2, K3: Relay_HJR-3FF-S-Z-5VDC; JW_Relay_Tianbo_HJR_3FF
R1, R6, R15: 680; JW_R_Axial_DIN0207_L6.3mm_D2.5mm_P10.16mm_Horizontal_SIlksc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
R2, R3, R4, R5, R7, R8, R9, R10, R11, R12, R13, R14, R19, R21: 220; JW_R_Axial_DIN0207_L6.3mm_D2.5mm_P10.16mm_Horizontal_SIlksc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
R16, R17: 1k5; JW_R_Axial_DIN0207_L6.3mm_D2.5mm_P10.16mm_Horizontal_SIlksc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
R18, R20, R22, R23: 2k2; JW_R_Axial_DIN0207_L6.3mm_D2.5mm_P10.16mm_Horizontal_SIlksc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
U1: LM1117-3.3; TO-220-3_Vertical
U2: L7805; TO-220-3_Vertical
U3: ESP32_Dev_Board_30Pin; JW_ESP32_DevKit_30Pin

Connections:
+3V3: C1.1, J3.2, J5.2, J8.5, J8.6, U1.2
+5V: Addressable RGB LED.3, C3.1, D1.1, D2.1, D3.1, J3.1, J5.1, J8.3, J8.4, K1.1, K2.1, K3.1, U2.3, U3.15
+12V: C2.1, F1.1, J7.7, J8.1, J8.2, JP1.2, JP2.2, JP3.2, U1.3, U2.1
/12V_BEFORE_FUSE: F1.2, J1.1
/RELAY1_C: J2.3, JP1.1, K1.3
/RELAY1_NC: J2.4, K1.4
/RELAY1_NO: J2.2, K1.5
/RELAY2_C: J4.3, JP2.1, K2.3
/RELAY2_NC: J4.4, K2.4
/RELAY2_NO: J4.2, K2.5
/RELAY3_C: J6.3, JP3.1, K3.3
/RELAY3_NC: J6.4, K3.4
/RELAY3_NO: J6.2, K3.5
GND: 2N3904.1, 2N3904#2.1, 2N3904#3.1, 2N3904#4.1, 2N3904#5.1, Addressable RGB LED.2, C1.2, C2.2, C3.2, J1.2, J2.1, J3.3, J4.1, J5.3, J6.1, J7.6, J8.7, J8.8, J8.9, J9.2, JP4.1, R22.2, R23.2, U1.1, U2.2, U3.14
unnamed: 2N3904#4.3, D1.2, K1.2
unnamed: 2N3904#3.3, D2.2, K2.2
unnamed: 2N3904#5.3, D3.2, K3.2
unnamed: Addressable RGB LED.4, U3.18
unnamed: J3.4, R2.2
unnamed: J3.5, R3.2
unnamed: J3.6, R4.2
unnamed: J3.7, R5.2
unnamed: J3.8, R7.2
unnamed: J3.9, R8.2
unnamed: J5.4, R9.2
unnamed: J5.5, R10.2
unnamed: J5.6, R11.2
unnamed: J5.7, R12.2
unnamed: J5.8, R13.2
unnamed: J5.9, R14.2
unnamed: J7.1, R19.1
unnamed: J7.2, R21.1
unnamed: J7.3, R16.1
unnamed: J7.4, R17.1
unnamed: J7.5, JP4.2
unnamed: J9.1, U3.24
unnamed: 2N3904#4.2, R1.1
unnamed: 2N3904#3.2, R6.1
unnamed: 2N3904#5.2, R15.1
unnamed: 2N3904#2.2, R18.2
unnamed: 2N3904#2.3, R19.2
unnamed: 2N3904.2, R20.2
unnamed: 2N3904.3, R21.2
unnamed: R1.2, U3.22
unnamed: R2.1, U3.6
unnamed: R6.2, U3.21
unnamed: R7.1, U3.29
unnamed: R8.1, U3.30
unnamed: R9.1, U3.7
unnamed: R3.1, R10.1, U3.8
unnamed: R4.1, R11.1, U3.9
unnamed: R5.1, R12.1, U3.10
unnamed: R13.1, U3.25
unnamed: R14.1, U3.26
unnamed: R15.2, U3.20
unnamed: R16.2, R22.1, U3.3
unnamed: R17.2, R23.1, U3.2
unnamed: R18.1, U3.13
unnamed: R20.1, U3.11

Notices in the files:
future/hardware/outside_board/heimdall_outsideboard.kicad_pcb:
License: MIT
